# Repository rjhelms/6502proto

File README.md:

# 6502 Protoboard

A prototyping board for experimenting with 6502 hardware and software design

This board implements a minimal 6502 system, containing a 65C02 processor, a 65C22 Versatile Interface Adapter (VIA), a 32kB EEPROM and 32kB of SRAM.

This project would not have been possible without Garth Wilson's excellent [6502 Primer](https://wilsonminesco.com/6502primer/index.html), which is eseential reading for anyone looking to get started with 6502 homebrew.

## Table of contents

- [Features](#features)
- [Building](#building)
- [Implementing address decoding](#implementing-address-decoding)
  - [Minimal setup](#minimal-setup)
  - [Adding more I/O](#adding-more-i-o)
- [Header pinouts](#header-pinouts)
  - [CPU signals](#cpu-signals)
  - [Address bus](#address-bus)
  - [CPU bus](#cpu-bus)
  - [VIA ports](#via-ports)
- [Useful links](#useful-links)

## Features

- Two clock sources: 1MHz crystal oscillator "fast" clock and 555-timer based "slow" clock (approx 0.5Hz - 500Hz)
- Blinkenlights for the address and data buses
- Header for external clock source, if desired
- 400-point breadboard area, for address decoding and other small circuits
- IDC headers for address & data buses, CPU signals, and both VIA ports

## Building

More to come - for now, refer to the [interactive BOM](https://rjhelms.github.io/6502proto/ibom.html).

## Implementing address decoding

In order to let the 6502 processor talk to other chips, any 6502 system requires some address decoding logic. The board has no address decoding built in; it is up to the builder to implement their chosen address decoding with the breadboard area.

Pads above the breadboard area provide access to the 4 highest bytes of the address bus, as well as the PH2 clock and R/W, and the relevant inputs for each of the on-board ICs.

The [address decoding chapter](https://wilsonminesco.com/6502primer/addr_decoding.html) of Garth Wilson's primer is well worth a read before deciding what to implement.

Some key considerations when choosing an address decoding scheme:

- Each address should select at most one device
- Writes to RAM should only occur when PH2 is high
- RAM should be at the bottom of the address space, to include the  zero  page ($0000-$00FF) and stack ($0100-$01FF).
- ROM should be at the top of the address space, to include the reset and interrupt vectors at $FFFA-$FFFF.

### Minimal setup

For a system only using the RAM, ROM, and VIA chips on board, satisfactory results can be achieved with a single 74HC00 quad NAND gate:

| Start | End   | Device |
|-------|-------|--------|
| $0000 | $7FFF | RAM    |
| $8000 | $BFFF | VIA    |
| $C000 | $FFFF | ROM    |

With only 64kB of address space and 32kB of both RAM and ROM, at least some portion of one of these will need to be masked by the VIA or other devices. This logic masks the lower half of ROM, resulting in a system with 32kB of RAM and 16kB of ROM.

A similar addressing scheme with 16kB of RAM and 32kB of ROM can also be implemented with one 74HC00.

### Adding more I/O

The minimal setup above works just fine for the chips on the protoboard, but doesn't leave any room for expanding the system any further. Also, while the VIA only needs 16 bytes of address space, the above setup allocates a whole 16kB to it!

By using a 74HC138 line decoder, that 16kB can be split into 8 2kB segments, each addressed by one output.

| Start | End   | Device |
|-------|-------|--------|
| $0000 | $7FFF | RAM    |
| $8000 | $87FF | (VIA) '138 output 0 |
...
| $B800 | $BFFF | '138 output 7 |
| $C000 | $FFFF | ROM    |

## Header pinouts

### CPU signals

| Pin | Signal | Pin | Signal |
|-----|--------|-----|--------|
| 1   | PH2    | 2   | PH2    |
| 3   | RESET  | 4   | RDY    |
| 5   | R/W    | 6   | IRQ    |
| 7   | unused | 8   | NMI    |
| 9   | unused | 10  | SYNC   |
| 11  | unused | 12  | BE     |
| 13  | 5V     | 14  | 5V     |
| 15  | GND    | 16  | GND    |

### Address bus

| Pin | Signal | Pin | Signal |
|-----|--------|-----|--------|
| 1   | A0     | 2   | A1     |
| 3   | A2     | 4   | A3     |
| 5   | A4     | 6   | A5     |
| 7   | A6     | 8   | A7     |
| 9   | A8     | 10  | A9     |
| 11  | A10    | 12  | A11    |
| 13  | A12    | 14  | A13    |
| 15  | A14    | 16  | A15    |

### CPU bus

| Pin | Signal | Pin | Signal |
|-----|--------|-----|--------|
| 1   | D0     | 2   | D1     |
| 3   | D2     | 4   | D3     |
| 5   | D4     | 6   | D5     |
| 7   | D6     | 8   | D7     |

### VIA ports

| Pin | Signal | Pin | Signal |
|-----|--------|-----|--------|
| 1   | 5V     | 2   | 5V     |
| 3   | PA0    | 4   | PA1    |
| 5   | PA2    | 6   | PA3    |
| 7   | PA4    | 8   | PA5    |
| 9   | PA6    | 10  | PA7    |
| 11  | CA1    | 12  | CA2    |
| 13  | GND    | 14  | GND    |

## Useful links

- [6502.org](http://6502.org/) - a wealth of information on 6502 hardware and software
- Garth Wilson's [6502 Primer](https://wilsonminesco.com/6502primer/index.html)
- Western Design Center, with datasheets and other useful info
  - [W65C02S 8-bit Microprocessor](https://www.westerndesigncenter.com/wdc/w65c02s-chip.php)
  - [W65C22 Versatile Interface Adapter (VIA)](https://www.westerndesigncenter.com/wdc/w65c22-chip.php)
- [cc65](https://cc65.github.io/), a 6502 C compiler and assembler

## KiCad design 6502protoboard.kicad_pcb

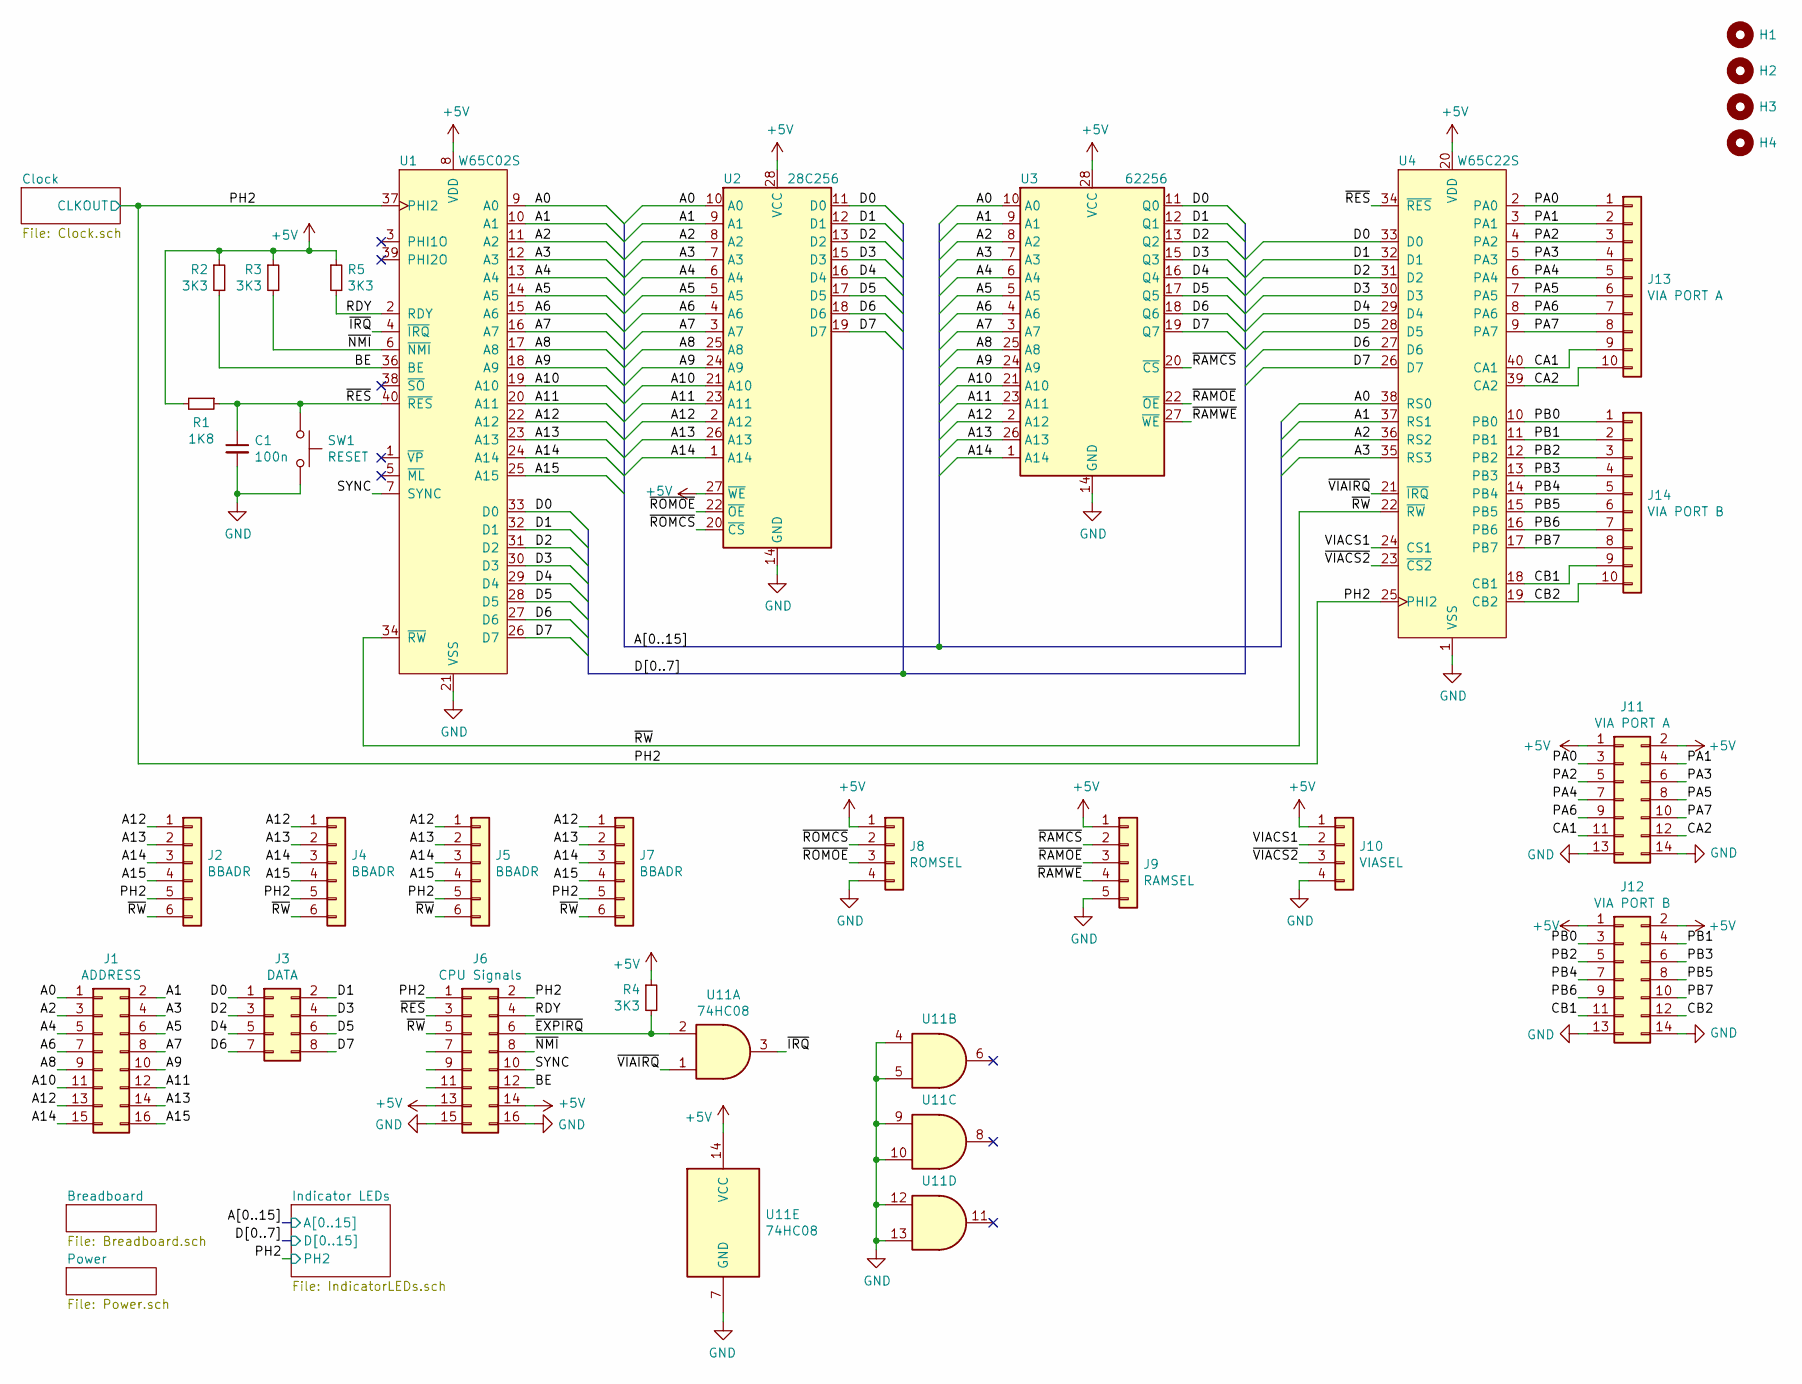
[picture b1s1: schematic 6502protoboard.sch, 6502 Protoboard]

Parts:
C1: 100n; C_Disc_D5.0mm_W2.5mm_P2.50mm
H1, H2, H3, H4: MountingHole; MountingHole_3.2mm_M3
J1, J6: Conn_02x08_Odd_Even; IDC-Header_2x08_P2.54mm_Vertical
J2, J4, J5, J7: Conn_01x05; PinHeader_1x06_P2.54mm_Vertical
J3: Conn_02x04_Odd_Even; IDC-Header_2x04_P2.54mm_Vertical
J8, J10: Conn_01x04; PinHeader_1x04_P2.54mm_Vertical
J9: Conn_01x05; PinHeader_1x05_P2.54mm_Vertical
J11, J12: Conn_02x07_Odd_Even; IDC-Header_2x07_P2.54mm_Vertical
J13, J14: Conn_01x10; PinHeader_1x10_P2.54mm_Vertical
R1: 1K8; R_Axial_DIN0207_L6.3mm_D2.5mm_P7.62mm_Horizontal
R2, R3, R4, R5: 3K3; R_Axial_DIN0207_L6.3mm_D2.5mm_P7.62mm_Horizontal
SW1: SW_Push; SW_TH_Tactile_Omron_B3F-10xx_Common_Pins
U1: W65C02S; DIP-40_W15.24mm_Socket_LongPads
U2: 28C256; DIP_Socket-28_W11.9_W12.7_W15.24_W17.78_W18.5_3M_228-1277-0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
U3: 62256; DIP-28_W15.24mm_Socket_LongPads
U4: W65C22S; DIP-40_W15.24mm_Socket_LongPads
U11: 74HC08; DIP-14_W7.62mm

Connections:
+5V: J6.13, J6.14, J8.1, J9.1, J10.1, J11.1, J11.2, J12.1, J12.2, R1.2, R2.1, R3.1, R4.1, R5.1, U1.8 (VDD), U2.27 (~WE), U2.28 (VCC), U3.28 (VCC), U4.20 (VDD), U11.14 (VCC); also elsewhere on the board
/A0: J1.1, U1.9 (A0), U2.10 (A0), U3.10 (A0), U4.38 (RS0); also elsewhere on the board
/A1: J1.2, U1.10 (A1), U2.9 (A1), U3.9 (A1), U4.37 (RS1); also elsewhere on the board
/A2: J1.3, U1.11 (A2), U2.8 (A2), U3.8 (A2), U4.36 (RS2); also elsewhere on the board
/A3: J1.4, U1.12 (A3), U2.7 (A3), U3.7 (A3), U4.35 (RS3); also elsewhere on the board
/A4: J1.5, U1.13 (A4), U2.6 (A4), U3.6 (A4); also elsewhere on the board
/A5: J1.6, U1.14 (A5), U2.5 (A5), U3.5 (A5); also elsewhere on the board
/A6: J1.7, U1.15 (A6), U2.4 (A6), U3.4 (A6); also elsewhere on the board
/A7: J1.8, U1.16 (A7), U2.3 (A7), U3.3 (A7); also elsewhere on the board
/A8: J1.9, U1.17 (A8), U2.25 (A8), U3.25 (A8); also elsewhere on the board
/A9: J1.10, U1.18 (A9), U2.24 (A9), U3.24 (A9); also elsewhere on the board
/A10: J1.11, U1.19 (A10), U2.21 (A10), U3.21 (A10); also elsewhere on the board
/A11: J1.12, U1.20 (A11), U2.23 (A11), U3.23 (A11); also elsewhere on the board
/A12: J1.13, J2.1, J4.1, J5.1, J7.1, U1.22 (A12), U2.2 (A12), U3.2 (A12); also elsewhere on the board
/A13: J1.14, J2.2, J4.2, J5.2, J7.2, U1.23 (A13), U2.26 (A13), U3.26 (A13); also elsewhere on the board
/A14: J1.15, J2.3, J4.3, J5.3, J7.3, U1.24 (A14), U2.1 (A14), U3.1 (A14); also elsewhere on the board
/A15: J1.16, J2.4, J4.4, J5.4, J7.4, U1.25 (A15); also elsewhere on the board
/BE: J6.12, R2.2, U1.36 (BE)
/CA1: J11.11, J13.9, U4.40 (CA1)
/CA2: J11.12, J13.10, U4.39 (CA2)
/CB1: J12.11, J14.9, U4.18 (CB1)
/CB2: J12.12, J14.10, U4.19 (CB2)
/D0: J3.1, U1.33 (D0), U2.11 (D0), U3.11 (Q0), U4.33 (D0); also elsewhere on the board
/D1: J3.2, U1.32 (D1), U2.12 (D1), U3.12 (Q1), U4.32 (D1); also elsewhere on the board
/D2: J3.3, U1.31 (D2), U2.13 (D2), U3.13 (Q2), U4.31 (D2); also elsewhere on the board
/D3: J3.4, U1.30 (D3), U2.15 (D3), U3.15 (Q3), U4.30 (D3); also elsewhere on the board
/D4: J3.5, U1.29 (D4), U2.16 (D4), U3.16 (Q4), U4.29 (D4); also elsewhere on the board
/D5: J3.6, U1.28 (D5), U2.17 (D5), U3.17 (Q5), U4.28 (D5); also elsewhere on the board
/D6: J3.7, U1.27 (D6), U2.18 (D6), U3.18 (Q6), U4.27 (D6); also elsewhere on the board
/D7: J3.8, U1.26 (D7), U2.19 (D7), U3.19 (Q7), U4.26 (D7); also elsewhere on the board
/PA0: J11.3, J13.1, U4.2 (PA0)
/PA1: J11.4, J13.2, U4.3 (PA1)
/PA2: J11.5, J13.3, U4.4 (PA2)
/PA3: J11.6, J13.4, U4.5 (PA3)
/PA4: J11.7, J13.5, U4.6 (PA4)
/PA5: J11.8, J13.6, U4.7 (PA5)
/PA6: J11.9, J13.7, U4.8 (PA6)
/PA7: J11.10, J13.8, U4.9 (PA7)
/PB0: J12.3, J14.1, U4.10 (PB0)
/PB1: J12.4, J14.2, U4.11 (PB1)
/PB2: J12.5, J14.3, U4.12 (PB2)
/PB3: J12.6, J14.4, U4.13 (PB3)
/PB4: J12.7, J14.5, U4.14 (PB4)
/PB5: J12.8, J14.6, U4.15 (PB5)
/PB6: J12.9, J14.7, U4.16 (PB6)
/PB7: J12.10, J14.8, U4.17 (PB7)
/PH2: J2.5, J4.5, J5.5, J6.1, J6.2, J7.5, U1.37 (PHI2), U4.25 (PHI2); also elsewhere on the board
/RDY: J6.4, R5.2, U1.2 (RDY)
/SYNC: J6.10, U1.7 (SYNC)
/VIACS1: J10.2, U4.24 (CS1)
/~EXPIRQ: J6.6, R4.2, U11.2
/~IRQ: U1.4 (~IRQ), U11.3
/~NMI: J6.8, R3.2, U1.6 (~NMI)
/~RAMCS: J9.2, U3.20 (~CS)
/~RAMOE: J9.3, U3.22 (~OE)
/~RAMWE: J9.4, U3.27 (~WE)
/~RES: C1.1, J6.3, R1.1, SW1.2, U1.40 (~RES), U4.34 (~RES)
/~ROMCS: J8.2, U2.20 (~CS)
/~ROMOE: J8.3, U2.22 (~OE)
/~RW: J2.6, J4.6, J5.6, J6.5, J7.6, U1.34 (~RW), U4.22 (~RW)
/~VIACS2: J10.3, U4.23 (~CS2)
/~VIAIRQ: U4.21 (~IRQ), U11.1
GND: C1.2, J6.15, J6.16, J8.4, J9.5, J10.4, J11.13, J11.14, J12.13, J12.14, SW1.1, U1.21 (VSS), U2.14 (GND), U3.14 (GND), U4.1 (VSS), U11.4, U11.5, U11.7 (GND), U11.9, U11.10, U11.12, U11.13; also elsewhere on the board

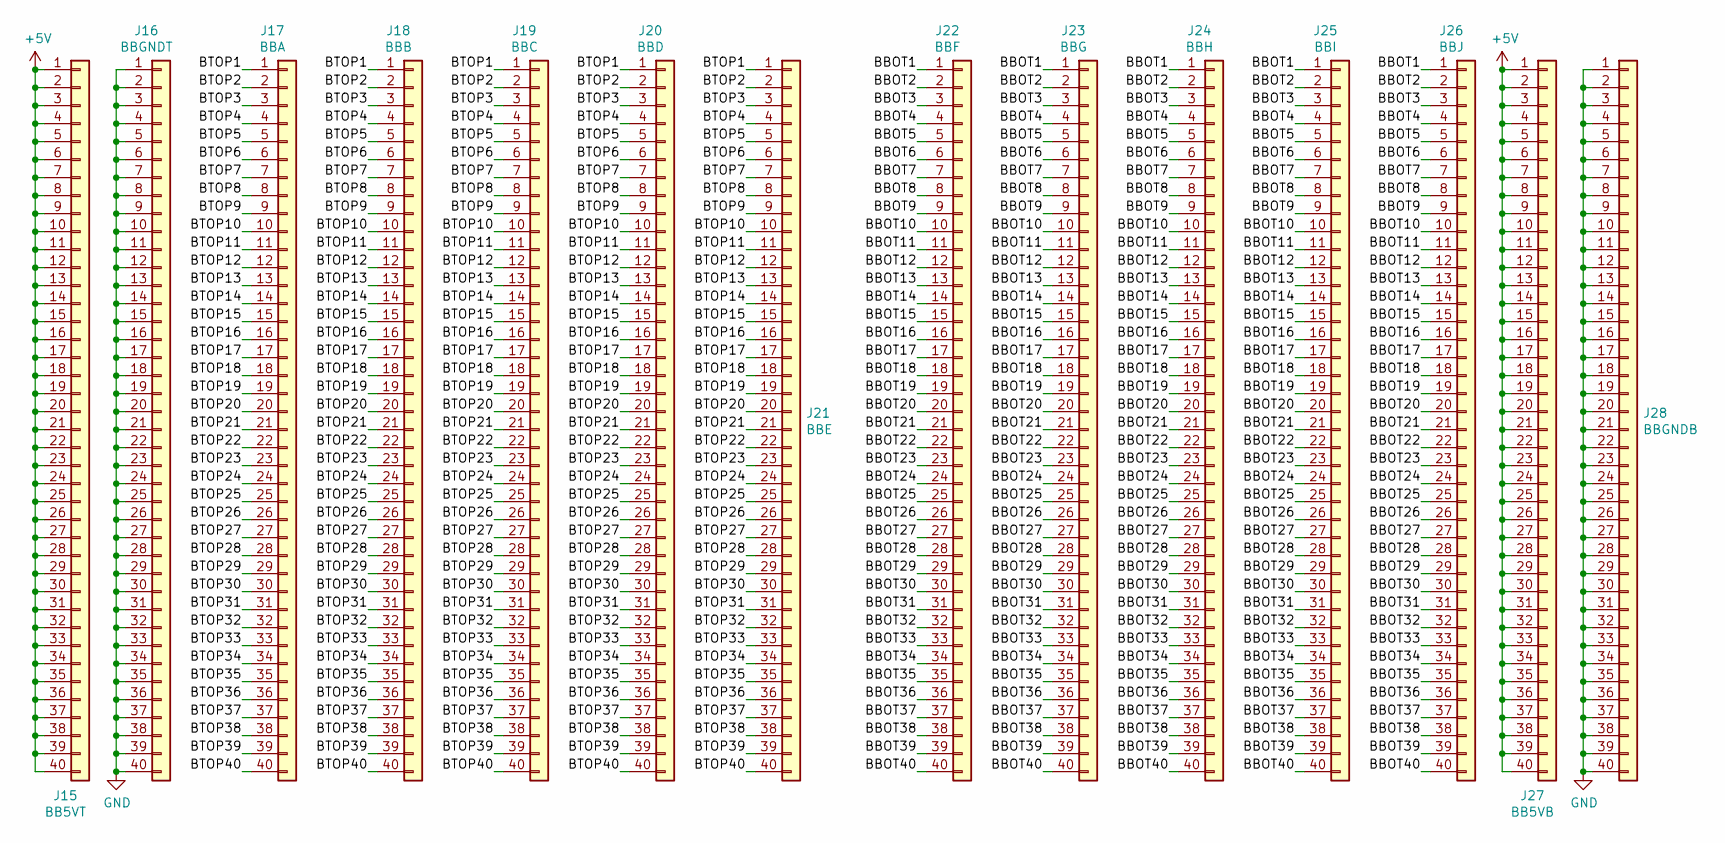
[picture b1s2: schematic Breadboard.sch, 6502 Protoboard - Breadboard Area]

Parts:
J15, J16, J17, J18, J19, J20, J21, J22, J23, J24, J25, J26, J27, J28: Conn_01x40; PinHeader_1x40_P2.54mm_Vertical

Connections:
+5V: J15.1, J15.2, J15.3, J15.4, J15.5, J15.6, J15.7, J15.8, J15.9, J15.10, J15.11, J15.12, J15.13, J15.14, J15.15, J15.16, J15.17, J15.18, J15.19, J15.20, J15.21, J15.22, J15.23, J15.24, J15.25, J15.26, J15.27, J15.28, J15.29, J15.30, J15.31, J15.32, J15.33, J15.34, J15.35, J15.36, J15.37, J15.38, J15.39, J15.40, J27.1, J27.2, J27.3, J27.4, J27.5, J27.6, J27.7, J27.8, J27.9, J27.10, J27.11, J27.12, J27.13, J27.14, J27.15, J27.16, J27.17, J27.18, J27.19, J27.20, J27.21, J27.22, J27.23, J27.24, J27.25, J27.26, J27.27, J27.28, J27.29, J27.30, J27.31, J27.32, J27.33, J27.34, J27.35, J27.36, J27.37, J27.38, J27.39, J27.40; also elsewhere on the board
/Breadboard/BBOT1: J22.1, J23.1, J24.1, J25.1, J26.1
/Breadboard/BBOT2: J22.2, J23.2, J24.2, J25.2, J26.2
/Breadboard/BBOT3: J22.3, J23.3, J24.3, J25.3, J26.3
/Breadboard/BBOT4: J22.4, J23.4, J24.4, J25.4, J26.4
/Breadboard/BBOT5: J22.5, J23.5, J24.5, J25.5, J26.5
/Breadboard/BBOT6: J22.6, J23.6, J24.6, J25.6, J26.6
/Breadboard/BBOT7: J22.7, J23.7, J24.7, J25.7, J26.7
/Breadboard/BBOT8: J22.8, J23.8, J24.8, J25.8, J26.8
/Breadboard/BBOT9: J22.9, J23.9, J24.9, J25.9, J26.9
/Breadboard/BBOT10: J22.10, J23.10, J24.10, J25.10, J26.10
/Breadboard/BBOT11: J22.11, J23.11, J24.11, J25.11, J26.11
/Breadboard/BBOT12: J22.12, J23.12, J24.12, J25.12, J26.12
/Breadboard/BBOT13: J22.13, J23.13, J24.13, J25.13, J26.13
/Breadboard/BBOT14: J22.14, J23.14, J24.14, J25.14, J26.14
/Breadboard/BBOT15: J22.15, J23.15, J24.15, J25.15, J26.15
/Breadboard/BBOT16: J22.16, J23.16, J24.16, J25.16, J26.16
/Breadboard/BBOT17: J22.17, J23.17, J24.17, J25.17, J26.17
/Breadboard/BBOT18: J22.18, J23.18, J24.18, J25.18, J26.18
/Breadboard/BBOT19: J22.19, J23.19, J24.19, J25.19, J26.19
/Breadboard/BBOT20: J22.20, J23.20, J24.20, J25.20, J26.20
/Breadboard/BBOT21: J22.21, J23.21, J24.21, J25.21, J26.21
/Breadboard/BBOT22: J22.22, J23.22, J24.22, J25.22, J26.22
/Breadboard/BBOT23: J22.23, J23.23, J24.23, J25.23, J26.23
/Breadboard/BBOT24: J22.24, J23.24, J24.24, J25.24, J26.24
/Breadboard/BBOT25: J22.25, J23.25, J24.25, J25.25, J26.25
/Breadboard/BBOT26: J22.26, J23.26, J24.26, J25.26, J26.26
/Breadboard/BBOT27: J22.27, J23.27, J24.27, J25.27, J26.27
/Breadboard/BBOT28: J22.28, J23.28, J24.28, J25.28, J26.28
/Breadboard/BBOT29: J22.29, J23.29, J24.29, J25.29, J26.29
/Breadboard/BBOT30: J22.30, J23.30, J24.30, J25.30, J26.30
/Breadboard/BBOT31: J22.31, J23.31, J24.31, J25.31, J26.31
/Breadboard/BBOT32: J22.32, J23.32, J24.32, J25.32, J26.32
/Breadboard/BBOT33: J22.33, J23.33, J24.33, J25.33, J26.33
/Breadboard/BBOT34: J22.34, J23.34, J24.34, J25.34, J26.34
/Breadboard/BBOT35: J22.35, J23.35, J24.35, J25.35, J26.35
/Breadboard/BBOT36: J22.36, J23.36, J24.36, J25.36, J26.36
/Breadboard/BBOT37: J22.37, J23.37, J24.37, J25.37, J26.37
/Breadboard/BBOT38: J22.38, J23.38, J24.38, J25.38, J26.38
/Breadboard/BBOT39: J22.39, J23.39, J24.39, J25.39, J26.39
/Breadboard/BBOT40: J22.40, J23.40, J24.40, J25.40, J26.40
/Breadboard/BTOP1: J17.1, J18.1, J19.1, J20.1, J21.1
/Breadboard/BTOP2: J17.2, J18.2, J19.2, J20.2, J21.2
/Breadboard/BTOP3: J17.3, J18.3, J19.3, J20.3, J21.3
/Breadboard/BTOP4: J17.4, J18.4, J19.4, J20.4, J21.4
/Breadboard/BTOP5: J17.5, J18.5, J19.5, J20.5, J21.5
/Breadboard/BTOP6: J17.6, J18.6, J19.6, J20.6, J21.6
/Breadboard/BTOP7: J17.7, J18.7, J19.7, J20.7, J21.7
/Breadboard/BTOP8: J17.8, J18.8, J19.8, J20.8, J21.8
/Breadboard/BTOP9: J17.9, J18.9, J19.9, J20.9, J21.9
/Breadboard/BTOP10: J17.10, J18.10, J19.10, J20.10, J21.10
/Breadboard/BTOP11: J17.11, J18.11, J19.11, J20.11, J21.11
/Breadboard/BTOP12: J17.12, J18.12, J19.12, J20.12, J21.12
/Breadboard/BTOP13: J17.13, J18.13, J19.13, J20.13, J21.13
/Breadboard/BTOP14: J17.14, J18.14, J19.14, J20.14, J21.14
/Breadboard/BTOP15: J17.15, J18.15, J19.15, J20.15, J21.15
/Breadboard/BTOP16: J17.16, J18.16, J19.16, J20.16, J21.16
/Breadboard/BTOP17: J17.17, J18.17, J19.17, J20.17, J21.17
/Breadboard/BTOP18: J17.18, J18.18, J19.18, J20.18, J21.18
/Breadboard/BTOP19: J17.19, J18.19, J19.19, J20.19, J21.19
/Breadboard/BTOP20: J17.20, J18.20, J19.20, J20.20, J21.20
/Breadboard/BTOP21: J17.21, J18.21, J19.21, J20.21, J21.21
/Breadboard/BTOP22: J17.22, J18.22, J19.22, J20.22, J21.22
/Breadboard/BTOP23: J17.23, J18.23, J19.23, J20.23, J21.23
/Breadboard/BTOP24: J17.24, J18.24, J19.24, J20.24, J21.24
/Breadboard/BTOP25: J17.25, J18.25, J19.25, J20.25, J21.25
/Breadboard/BTOP26: J17.26, J18.26, J19.26, J20.26, J21.26
/Breadboard/BTOP27: J17.27, J18.27, J19.27, J20.27, J21.27
/Breadboard/BTOP28: J17.28, J18.28, J19.28, J20.28, J21.28
/Breadboard/BTOP29: J17.29, J18.29, J19.29, J20.29, J21.29
/Breadboard/BTOP30: J17.30, J18.30, J19.30, J20.30, J21.30
/Breadboard/BTOP31: J17.31, J18.31, J19.31, J20.31, J21.31
/Breadboard/BTOP32: J17.32, J18.32, J19.32, J20.32, J21.32
/Breadboard/BTOP33: J17.33, J18.33, J19.33, J20.33, J21.33
/Breadboard/BTOP34: J17.34, J18.34, J19.34, J20.34, J21.34
/Breadboard/BTOP35: J17.35, J18.35, J19.35, J20.35, J21.35
/Breadboard/BTOP36: J17.36, J18.36, J19.36, J20.36, J21.36
/Breadboard/BTOP37: J17.37, J18.37, J19.37, J20.37, J21.37
/Breadboard/BTOP38: J17.38, J18.38, J19.38, J20.38, J21.38
/Breadboard/BTOP39: J17.39, J18.39, J19.39, J20.39, J21.39
/Breadboard/BTOP40: J17.40, J18.40, J19.40, J20.40, J21.40
GND: J16.1, J16.2, J16.3, J16.4, J16.5, J16.6, J16.7, J16.8, J16.9, J16.10, J16.11, J16.12, J16.13, J16.14, J16.15, J16.16, J16.17, J16.18, J16.19, J16.20, J16.21, J16.22, J16.23, J16.24, J16.25, J16.26, J16.27, J16.28, J16.29, J16.30, J16.31, J16.32, J16.33, J16.34, J16.35, J16.36, J16.37, J16.38, J16.39, J16.40, J28.1, J28.2, J28.3, J28.4, J28.5, J28.6, J28.7, J28.8, J28.9, J28.10, J28.11, J28.12, J28.13, J28.14, J28.15, J28.16, J28.17, J28.18, J28.19, J28.20, J28.21, J28.22, J28.23, J28.24, J28.25, J28.26, J28.27, J28.28, J28.29, J28.30, J28.31, J28.32, J28.33, J28.34, J28.35, J28.36, J28.37, J28.38, J28.39, J28.40; also elsewhere on the board

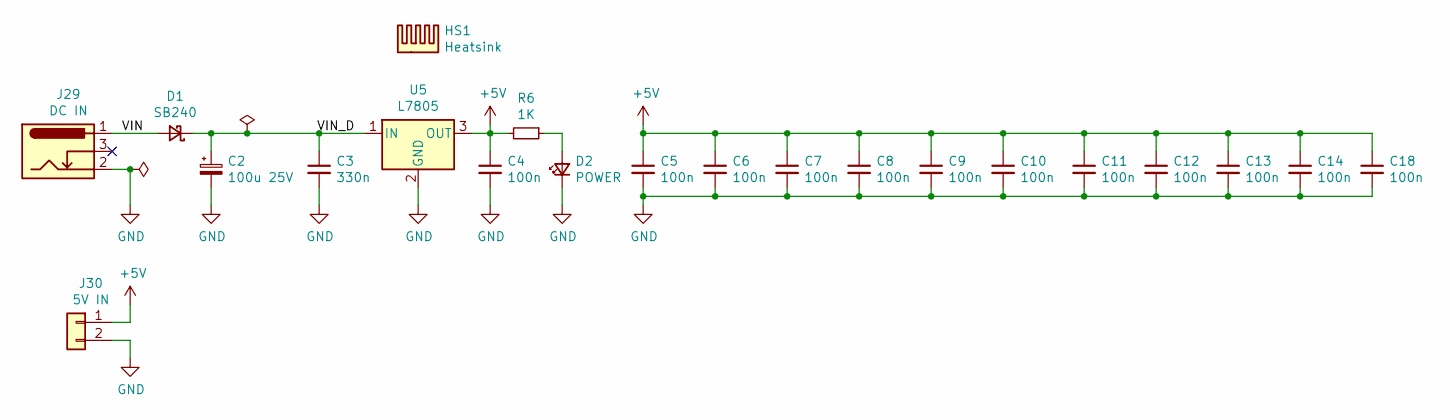
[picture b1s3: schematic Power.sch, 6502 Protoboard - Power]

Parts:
C2: 100u 25V; CP_Radial_D6.3mm_P2.50mm
C3: 330n; C_Disc_D5.0mm_W2.5mm_P2.50mm
C4, C5, C6, C7, C8, C9, C10, C11, C12, C13, C14, C18: 100n; C_Disc_D5.0mm_W2.5mm_P2.50mm
D1: SB240; D_DO-15_P10.16mm_Horizontal
D2: LED; LED_D5.0mm
HS1: Heatsink; Heatsink_Assman_V4330N
J29: Barrel_Jack_Switch; BarrelJack_Wuerth_6941xx301002
J30: Conn_01x02; PinHeader_1x02_P2.54mm_Vertical
R6: 1K; R_Axial_DIN0207_L6.3mm_D2.5mm_P7.62mm_Horizontal
U5: L7805; TO-220-3_Vertical

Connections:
+5V: C4.1, C5.1, C6.1, C7.1, C8.1, C9.1, C10.1, C11.1, C12.1, C13.1, C14.1, C18.1, J30.1, R6.2, U5.3 (OUT); also elsewhere on the board
/Power/VIN: D1.2 (A), J29.1
/Power/VIN_D: C2.1, C3.1, D1.1 (K), U5.1 (IN)
GND: C2.2, C3.2, C4.2, C5.2, C6.2, C7.2, C8.2, C9.2, C10.2, C11.2, C12.2, C13.2, C14.2, C18.2, D2.1 (K), J29.2, J30.2, U5.2 (GND); also elsewhere on the board
unnamed: D2.2 (A), R6.1

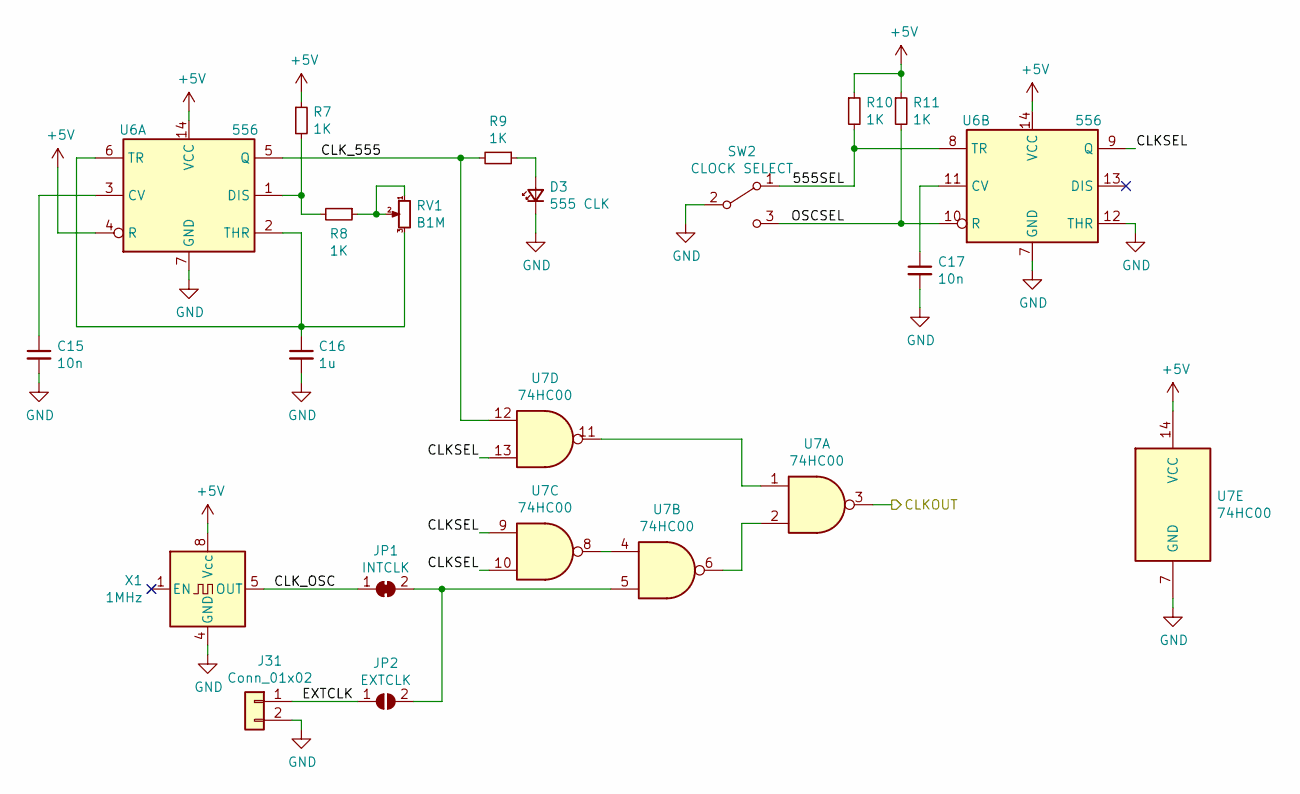
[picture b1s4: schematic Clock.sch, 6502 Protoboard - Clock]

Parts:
C15, C17: 10n; C_Disc_D5.0mm_W2.5mm_P2.50mm
C16: 1u; C_Disc_D5.0mm_W2.5mm_P2.50mm
D3: LED; LED_D5.0mm
J31: Conn_01x02; PinHeader_1x02_P2.54mm_Vertical
JP1: SolderJumper_2_Open; SolderJumper-2_P1.3mm_Bridged_RoundedPad1.0x1.5mm
JP2: SolderJumper_2_Bridged; SolderJumper-2_P1.3mm_Open_RoundedPad1.0x1.5mm
R7, R8, R9, R10, R11: 1K; R_Axial_DIN0207_L6.3mm_D2.5mm_P7.62mm_Horizontal
RV1: B1M; Potentiometer_Alpha_RD901F-40-00D_Single_Vertical_Centered
SW2: SW_SPDT; SW_SPDT_E-Switch_200MSP1xM2
U6: 556; DIP-14_W7.62mm_LongPads
U7: 74HC00; DIP-14_W7.62mm
X1: 1MHz; Oscillator_DIP-8

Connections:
+5V: R7.1, R10.1, R11.1, U6.4 (R), U6.14 (VCC), U7.14 (VCC), X1.8 (Vcc); also elsewhere on the board
/Clock/555SEL: R10.2, SW2.1 (A), U6.8 (TR)
/Clock/CLKSEL: U6.9 (Q), U7.9, U7.10, U7.13
/Clock/CLK_555: R9.2, U6.5 (Q), U7.12
/Clock/CLK_OSC: JP1.1 (A), X1.5 (OUT)
/Clock/EXTCLK: J31.1, JP2.1 (A)
/Clock/OSCSEL: R11.2, SW2.3 (C), U6.10 (R)
/PH2: U7.3; also elsewhere on the board
GND: C15.2, C16.2, C17.2, D3.1 (K), J31.2, SW2.2 (B), U6.7 (GND), U6.12 (THR), U7.7 (GND), X1.4 (GND); also elsewhere on the board
unnamed: C15.1, U6.3 (CV)
unnamed: C16.1, RV1.3, U6.2 (THR), U6.6 (TR)
unnamed: C17.1, U6.11 (CV)
unnamed: D3.2 (A), R9.1
unnamed: JP1.2 (B), JP2.2 (B), U7.5
unnamed: R7.2, R8.2, U6.1 (DIS)
unnamed: R8.1, RV1.1, RV1.2
unnamed: U7.1, U7.11
unnamed: U7.2, U7.6
unnamed: U7.4, U7.8

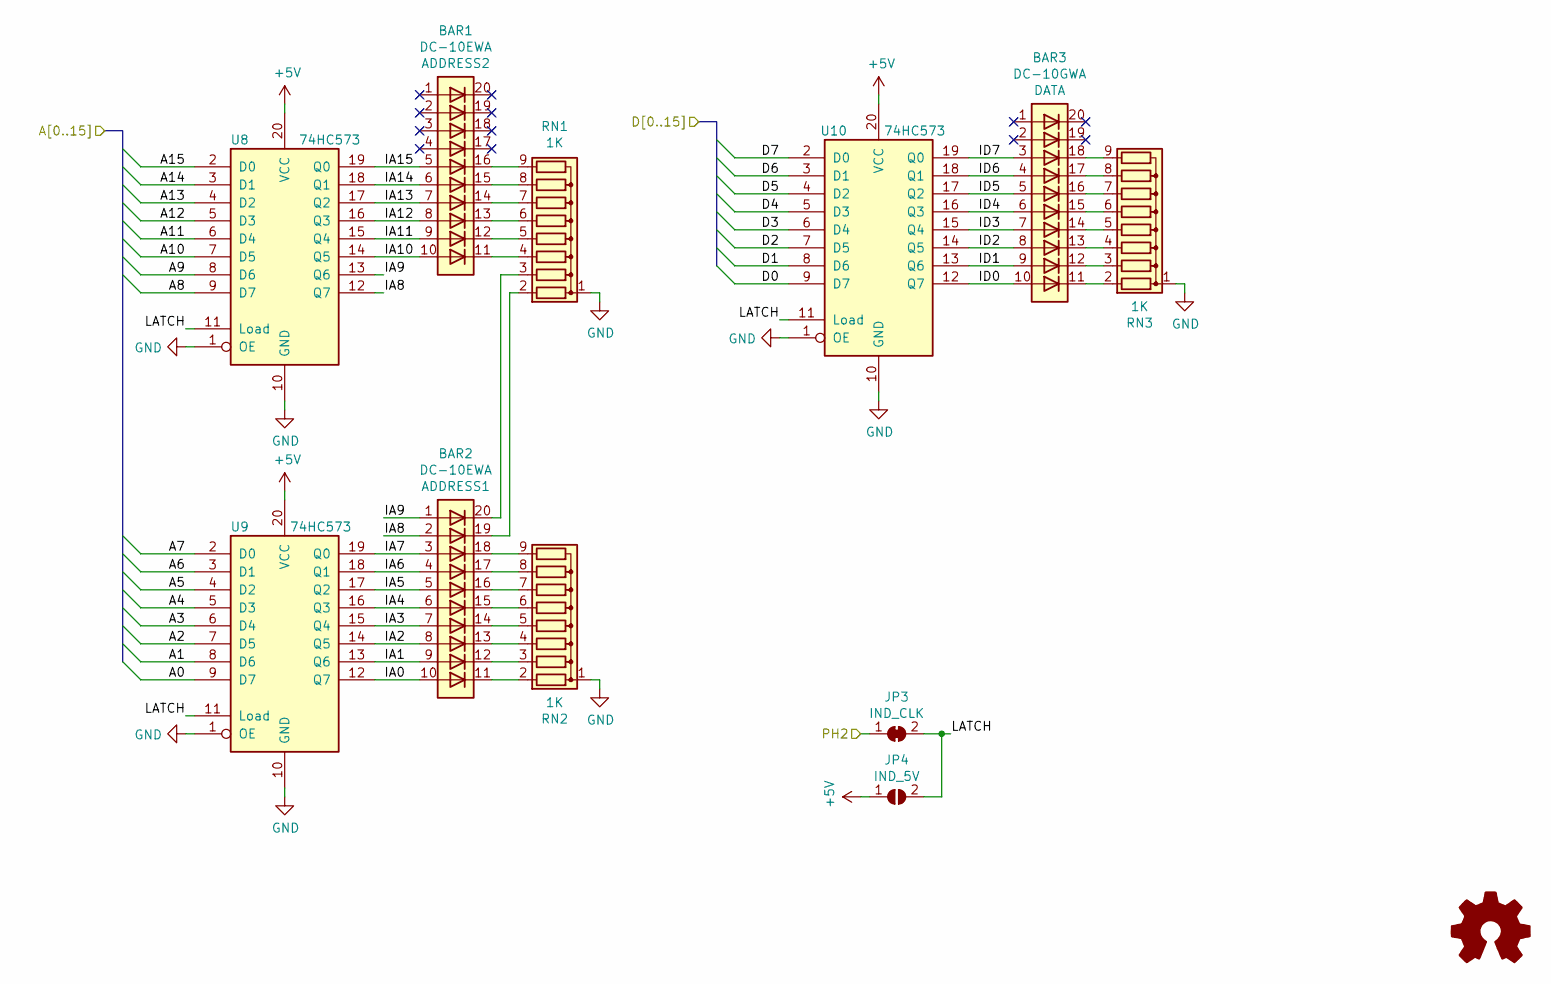
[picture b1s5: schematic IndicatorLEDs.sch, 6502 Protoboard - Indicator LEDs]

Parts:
BAR1, BAR2: DC-10EWA; HDSP-4830
BAR3: DC-10GWA; HDSP-4850
JP3: SolderJumper_Bridged; SolderJumper-2_P1.3mm_Bridged_RoundedPad1.0x1.5mm
JP4: SolderJumper_Open; SolderJumper-2_P1.3mm_Open_RoundedPad1.0x1.5mm
LOGO1: Logo_Open_Hardware_Small; OSHW-Logo_5.7x6mm_SilkScreen
RN1, RN2, RN3: 1K; R_Array_SIP9
U8, U9, U10: 74HC573; DIP-20_W7.62mm

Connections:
+5V: JP4.1 (A), U8.20 (VCC), U9.20 (VCC), U10.20 (VCC); also elsewhere on the board
/A0: U9.9 (D7); also elsewhere on the board
/A1: U9.8 (D6); also elsewhere on the board
/A2: U9.7 (D5); also elsewhere on the board
/A3: U9.6 (D4); also elsewhere on the board
/A4: U9.5 (D3); also elsewhere on the board
/A5: U9.4 (D2); also elsewhere on the board
/A6: U9.3 (D1); also elsewhere on the board
/A7: U9.2 (D0); also elsewhere on the board
/A8: U8.9 (D7); also elsewhere on the board
/A9: U8.8 (D6); also elsewhere on the board
/A10: U8.7 (D5); also elsewhere on the board
/A11: U8.6 (D4); also elsewhere on the board
/A12: U8.5 (D3); also elsewhere on the board
/A13: U8.4 (D2); also elsewhere on the board
/A14: U8.3 (D1); also elsewhere on the board
/A15: U8.2 (D0); also elsewhere on the board
/D0: U10.9 (D7); also elsewhere on the board
/D1: U10.8 (D6); also elsewhere on the board
/D2: U10.7 (D5); also elsewhere on the board
/D3: U10.6 (D4); also elsewhere on the board
/D4: U10.5 (D3); also elsewhere on the board
/D5: U10.4 (D2); also elsewhere on the board
/D6: U10.3 (D1); also elsewhere on the board
/D7: U10.2 (D0); also elsewhere on the board
/Indicator LEDs/IA0: BAR2.10 (A), U9.12 (Q7)
/Indicator LEDs/IA1: BAR2.9 (A), U9.13 (Q6)
/Indicator LEDs/IA2: BAR2.8 (A), U9.14 (Q5)
/Indicator LEDs/IA3: BAR2.7 (A), U9.15 (Q4)
/Indicator LEDs/IA4: BAR2.6 (A), U9.16 (Q3)
/Indicator LEDs/IA5: BAR2.5 (A), U9.17 (Q2)
/Indicator LEDs/IA6: BAR2.4 (A), U9.18 (Q1)
/Indicator LEDs/IA7: BAR2.3 (A), U9.19 (Q0)
/Indicator LEDs/IA8: BAR2.2 (A), U8.12 (Q7)
/Indicator LEDs/IA9: BAR2.1 (A), U8.13 (Q6)
/Indicator LEDs/IA10: BAR1.10 (A), U8.14 (Q5)
/Indicator LEDs/IA11: BAR1.9 (A), U8.15 (Q4)
/Indicator LEDs/IA12: BAR1.8 (A), U8.16 (Q3)
/Indicator LEDs/IA13: BAR1.7 (A), U8.17 (Q2)
/Indicator LEDs/IA14: BAR1.6 (A), U8.18 (Q1)
/Indicator LEDs/IA15: BAR1.5 (A), U8.19 (Q0)
/Indicator LEDs/ID0: BAR3.10 (A), U10.12 (Q7)
/Indicator LEDs/ID1: BAR3.9 (A), U10.13 (Q6)
/Indicator LEDs/ID2: BAR3.8 (A), U10.14 (Q5)
/Indicator LEDs/ID3: BAR3.7 (A), U10.15 (Q4)
/Indicator LEDs/ID4: BAR3.6 (A), U10.16 (Q3)
/Indicator LEDs/ID5: BAR3.5 (A), U10.17 (Q2)
/Indicator LEDs/ID6: BAR3.4 (A), U10.18 (Q1)
/Indicator LEDs/ID7: BAR3.3 (A), U10.19 (Q0)
/Indicator LEDs/LATCH: JP3.2 (B), JP4.2 (B), U8.11 (Load), U9.11 (Load), U10.11 (Load)
/PH2: JP3.1 (A); also elsewhere on the board
GND: RN1.1 (common), RN2.1 (common), RN3.1 (common), U8.1 (OE), U8.10 (GND), U9.1 (OE), U9.10 (GND), U10.1 (OE), U10.10 (GND); also elsewhere on the board
unnamed: BAR1.11 (K), RN1.4 (R3)
unnamed: BAR1.12 (K), RN1.5 (R4)
unnamed: BAR1.13 (K), RN1.6 (R5)
unnamed: BAR1.14 (K), RN1.7 (R6)
unnamed: BAR1.15 (K), RN1.8 (R7)
unnamed: BAR1.16 (K), RN1.9 (R8)
unnamed: BAR2.11 (K), RN2.2 (R1)
unnamed: BAR2.12 (K), RN2.3 (R2)
unnamed: BAR2.13 (K), RN2.4 (R3)
unnamed: BAR2.14 (K), RN2.5 (R4)
unnamed: BAR2.15 (K), RN2.6 (R5)
unnamed: BAR2.16 (K), RN2.7 (R6)
unnamed: BAR2.17 (K), RN2.8 (R7)
unnamed: BAR2.18 (K), RN2.9 (R8)
unnamed: BAR2.19 (K), RN1.2 (R1)
unnamed: BAR2.20 (K), RN1.3 (R2)
unnamed: BAR3.11 (K), RN3.2 (R1)
unnamed: BAR3.12 (K), RN3.3 (R2)
unnamed: BAR3.13 (K), RN3.4 (R3)
unnamed: BAR3.14 (K), RN3.5 (R4)
unnamed: BAR3.15 (K), RN3.6 (R5)
unnamed: BAR3.16 (K), RN3.7 (R6)
unnamed: BAR3.17 (K), RN3.8 (R7)
unnamed: BAR3.18 (K), RN3.9 (R8)

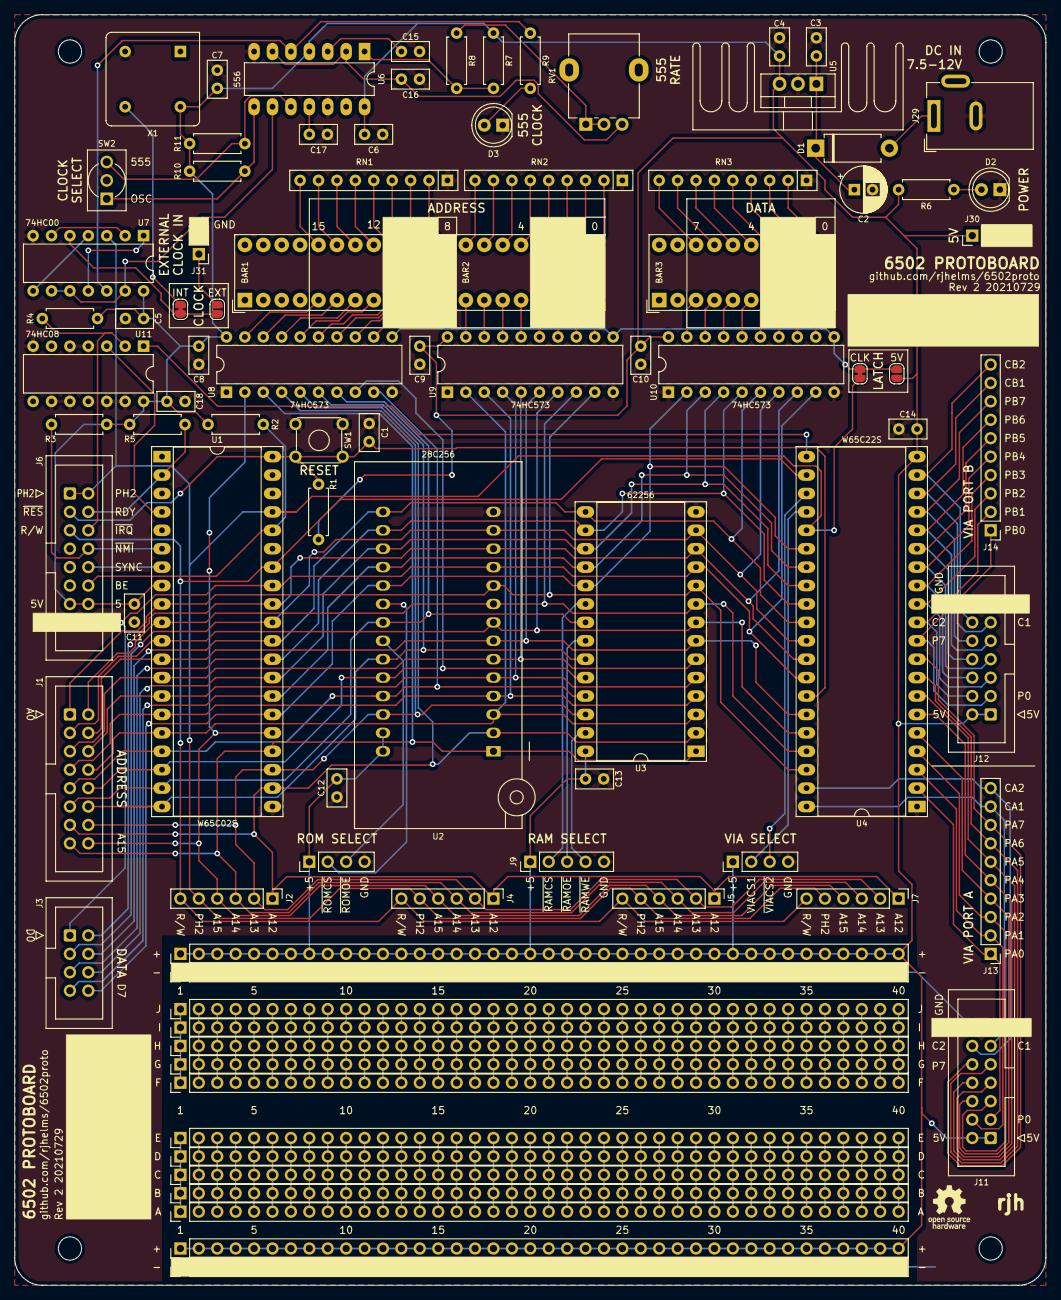
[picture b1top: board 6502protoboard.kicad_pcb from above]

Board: 2 copper layers, 142.2 x 175.3 mm, 95 parts (1 on the bottom side), 211 nets.

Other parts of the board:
LOGO1#2: Logo_Open_Hardware_Small; OSHW-Logo_5.7x6mm_SilkScreen

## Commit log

2021-08-12 Commit kicad project at Rev2
2021-08-12 Add github URL to kicad project
2021-08-12 Add license
2021-08-12 Replace image
2021-08-13 Fix power schematic page size
2021-08-13 Expand REAME
2021-08-13 Add PDF schematic
2021-08-13 Add ibom
2021-08-13 Update README.md
    Fix typo

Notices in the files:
6502protoboard.kicad_pcb:
CC BY-SA 4.0
README.md:
License: CC BY-SA 4.0
